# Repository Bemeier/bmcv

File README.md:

# BMCV

Eight scene-crossfaded LFOs in 16HP, with a PLL that locks them to an incoming
clock. This repository is the firmware, and three other things that run the
*same* firmware: a headless simulator, a browser frontend, and a VCV Rack
module.

**[bemeier.github.io/bmcv](https://bemeier.github.io/bmcv/)** is that frontend,
built and deployed from `main`. It runs the module with no install, shows a
physical one over USB if you have the hardware, and carries the
[manual](https://bemeier.github.io/bmcv/manual/), a
[firmware updater](https://bemeier.github.io/bmcv/update/) and a
[diagnostics page](https://bemeier.github.io/bmcv/diagnostics/).

How to *play* the module is the manual's job, not this file's. What follows is
how the project is put together.

## One core, four hosts

Everything that behaves like a BMCV runs `Core/Src/Lib` unmodified - the same
`engine_tick`, the same UX layer, the same LED renderer. Nothing below
reimplements any of it, and none of them may: a host supplies time, input and
somewhere to put the output, and that is the whole contract.

| | what it is | lives in |
|---|---|---|
| **Firmware** | The module. STM32G474, one `bmcv_main()` off a 250µs tick. | `Core/Src/` |
| **Simulator** | The same core behind a flat C API, plus a scripting CLI for golden-file runs. | `sim/` |
| **Web frontend** | That API compiled to wasm, with an SVG panel and scopes over it. | `web/` |
| **VCV Rack** | A Rack module wrapping the same core. | `vcv/` |

The consequence worth knowing: the browser page is not a *model* of the module,
it is the module's own code with a different set of peripherals bolted on. That
is what lets the same page decode a real module's memory - see
[docs/live-module.md](docs/live-module.md) - with no parser and no second copy
of any unit conversion.

[docs/architecture.md](docs/architecture.md) is the long version.

## Repository layout

    Core/Src/Lib/     the core: engine, UX layer, LED renderer. No hardware.
    Core/Src/         the firmware's own half: ADCs, DAC, FRAM, USB, main loop.
    USB_Device/       the USB stack's app layer - descriptors, WebUSB, DFU entry.
    Middlewares/      ST's USB device library, with the MIDI class extended.

    sim/              the flat C API, its runtime shims and the scripting CLI.
    web/              the browser frontend: simulator, manual, updater, diagnostics.
    vcv/              the VCV Rack plugin.

    tests/            host-compiled tests over Core/Src/Lib and the USB descriptors.
    tools/            code generators - the panel spec, the layout asserts.
    panel/            the generated panel spec, shared by every host.
    pcb/              the KiCad project; production/ holds its fab outputs.
    docs/             architecture, the PLL, the wavetable, the live link, setup.

`Core/Src/Lib` never includes a HAL header. That is what makes the same files
compile for ARM, for the host tests, for wasm and for Rack - and it holds
because three of those four toolchains have no STM32 headers at all.

## Hardware

BMCV is a real Eurorack module - a Macro CV Controller inspired by the
[Emblematic Systems Catalyst](http://www.emblematic-systems.net/). The PCB is
made with [KiCad 8.0](https://www.kicad.org/); the project lives in
[`pcb/`](pcb/) and its fabrication outputs (BOM, gerbers, pick-and-place) in
[`production/`](production/).

![Render][render]

Eight output jacks and four input jacks, eight endless encoders that are also
buttons, nine control buttons, seven scene buttons, a crossfader, and 21
WS2812s. One USB-C port, which is a MIDI port and a vendor interface at once -
[docs/midi.md](docs/midi.md), [docs/live-module.md](docs/live-module.md).

The panel geometry is not typed in anywhere. `tools/gen_panel_spec.py` reads the
KiCad placement data and the firmware's own index tables and writes `panel/`,
which every host then draws from - so the picture on the web page cannot drift
from the board.

## The concepts the design turns on

Three, and most of the codebase follows from them.

**A channel is an oscillator locked to a ratio, not a rate.** Frequencies are
divisions of the incoming beat, so a patch stays in phase with everything around
it. That is why there is a PLL rather than a tempo readout, and why
`clock_sync.c` is the most carefully tested file here -
[docs/pll.md](docs/pll.md).

**A scene is every parameter of every channel at once, and the crossfader blends
two of them.** Forty-eight values move on one fader. That is why parameters live
in a scene-indexed array rather than on the channel, and why `EngineConfig` is
the thing that gets saved, copied and cleared.

**The whole module is one struct.** `BmcvInstance` holds the config, the signal
path, the interaction state and the input layer; the firmware keeps exactly one.
Nothing that matters lives in a file-static. That is what lets a host run
several, a test build one per case, and a debug probe or a USB link ship the
entire module to a browser as bytes.

## LED language

The colours are not decoration. One fact per LED, and the same colour for the
same idea on every page - the point being that the panel teaches itself, so the
manual never has to explain a colour.

- **Ctrl-page settings clamp, they do not wrap.** Each is a short list of
  unrelated states with its default at index 0, so spinning an encoder fully
  left resets it and you can do that without looking. Rolling off one end into
  the other would be the largest change on the page.
- **Setting states** are the base layer. Index 0 of every setting - disabled,
  default, neutral - is **purple**; **cyan** is continuous / level-following or
  multiplicative, **green** additive or half-way, **yellow** triggered / clocked
  / stepped, **red** reset. Destructive is **pink**, and belongs to clearing
  alone. See `HUE_STATE_*` in `color_presets.h`. The output clamp is the one
  place brightness also carries meaning, because it is two facts on one LED.
- **White is assignment, and nothing else uses it.** A short white flash every
  1.6s over an element's own colour means "you can pick this". Once something is
  held, the places it can go are steady white with a short dropout, the held
  source is steady saturated purple, and everything else goes **dark** - if it
  cannot be pressed it does not light.
- **Output level** only appears when no shift mode is active. In a shift mode
  the encoder ring shows that mode's setting, or nothing if it has none.
- **FRQ is a ratio, not a level**, so its ring codes three facts on three axes
  rather than drawing a bar. **Hue** is the kind of division: **green** straight
  (halves, quarters, octaves), **yellow** triplet, **orange** quintuplet -
  octaves are free, so 1/8 and 16 are the same green and 1/3, 3/2 and 24 are the
  same yellow. **Saturation** is how far off the grid the value sits, so a fine
  adjust washes the colour out to a pastel and a snapped ratio is pure.
  **Brightness** pulses shallowly at the channel's own output rate, which is
  what says fast from slow; anything too fast for the panel to resolve shimmers
  together at one rate instead of aliasing into a slow phantom pulse.
- **Confirmations** are a brief flash on top: purple wrote, pink cleared, cyan
  loaded. Purple is the selection colour, so a copy landing somewhere flashes
  the colour the source was held in. Red is errors only.
- **A held press dips out once as it crosses each of its thresholds** - off,
  then back on - which says "that registered" rather than pulsing away as if
  something were still in progress. At the first stage it comes back exactly as
  the page had it; where holding longer does something wider - clearing every
  scene rather than this one - it comes back brighter, in the same colour.
  Nothing commits until the release.

## Building

Prerequisites, what each fetch recipe actually gets and why, and
troubleshooting: [docs/setup.md](docs/setup.md). On a fresh checkout, the one
thing to run first is `just arm-sdk`.

    just arm-sdk          # fetch the ARM toolchain + STM32Cube HAL, once
    just build            # ARM firmware        just flash / just flash-usb
    just check            # everything host-side: format, tests, flows, wasm, web
    just check-all        # the above plus the firmware and Rack plugin builds
    just test-san         # the same tests under ASan/UBSan
    just fmt              # clang-format the hand-written C (fmt-check to verify)
    just web              # the browser frontend, at http://localhost:8000
    just docs-page        # the same pages with no wasm build, for the updater
    just vcv-install      # build the Rack plugin into ~/.local/share/Rack2
    just vcv-dist win-x64 # a distributable .vcvplugin for any platform

    # Rack running on Windows while you build in WSL. Needs the cross-compiler
    # once: sudo apt install gcc-mingw-w64-x86-64 g++-mingw-w64-x86-64
    just vcv-win-install  # cross-build plugin.dll into %LOCALAPPDATA%\Rack2

    just panel            # regenerate the panel spec from the hardware repo
    just layout-check     # regenerate the struct layout asserts from the ELF
    just docs-shots       # regenerate the screenshots in this file
    just dfu-check        # check the DfuSe client against a fake device

`just fmt` is pinned to clang-format 18, which is what CI installs; the recipe
refuses any other major, because the output moves between them.

Anything machine-specific - where your Rack SDK lives, which browser to drive -
goes in `local.just`, which is not checked in. `CMakeLists.txt` has the same
arrangement with `local.cmake`.

CI runs `just check`, the sanitizer pass and an ARM build on every push - one
job per target, in [`.github/workflows/ci.yml`](.github/workflows/ci.yml). The
firmware size is printed into the job summary rather than gated.

A push to `main` that clears every job bumps `VERSION` and `CHANGELOG.md` from
the commits since the last tag and cuts a GitHub Release - see
[Versioning](#versioning). The same push deploys `web/` to GitHub Pages.

## Flashing

Three routes, and they want different files.

**Over the programming header, from a build.** `just flash` sends
`build/BMCVFirmware.elf` over an ST-Link; `just flash-rel` does the same with
the release build. It needs the module out of the rack with a ribbon on its
debug header, and it is the only route that can also halt the core - so it is
what `just where` and any breakpoint work sit on.

**Over USB-C, from a build.** `just flash-usb` sends `build/BMCVFirmware.bin`
through the STM32's ROM DFU bootloader, with no probe and **the module still in
the rack**. That is the development loop when nothing needs stepping through:
the WebUSB link and the diagnostics page still work, so printf-level debugging
survives; halting does not. The module has to be put into update mode first -
hold **CPY** while it powers up, or press the update-mode button on the updater
page - and the recipe says which, then waits for the bootloader to appear. See
[docs/setup.md](docs/setup.md).

**Over USB-C, from the browser.**
[bemeier.github.io/bmcv/update](https://bemeier.github.io/bmcv/update/) flashes
a released version or a local `.bin`, with no build and no probe. `just
docs-page` serves the same page locally against your own build. That page
documents the rest - what to hold, what Windows needs once, what the panel does
- and this file does not repeat it.

It has to be the `.bin` there. The `.elf` beside it is what the ST-Link path
wants and is not a raw image: headers and symbols, so its first bytes are not
the vector table, and a debug build is four times the size of the flash. The
updater checks for this and refuses, naming the mistake, before erasing
anything.

Both files are on every [release](https://github.com/Bemeier/bmcv/releases). The
`.elf` is the same build with its symbols still attached, which is what a
debugger or a live variable viewer needs to attach to a module running that
release - a `.bin` carries no symbol table, so no tool can find a variable in
one. Take the `.elf` from the release the module is actually running, since
every address in it belongs to that build.

## Installing the Rack module without building it

Every [release](https://github.com/Bemeier/bmcv/releases) carries a
`BMCV-<version>-<platform>.vcvplugin` for `lin-x64`, `win-x64`, `mac-x64` and
`mac-arm64`. Drop the one for your platform into Rack's plugin folder and
restart Rack, which unpacks it on the way up. The folder ends in your
platform's name - since Rack 2.4 there is one per platform, and a plain
`plugins` directory is not read:

| | |
|---|---|
| Windows | `%LOCALAPPDATA%\Rack2\plugins-win-x64` |
| macOS (Apple silicon) | `~/Library/Application Support/Rack2/plugins-mac-arm64` |
| macOS (Intel) | `~/Library/Application Support/Rack2/plugins-mac-x64` |
| Linux | `~/.local/share/Rack2/plugins-lin-x64` |

It is not in the VCV Library, so nothing has signed it but this repository's
CI. On macOS that means Gatekeeper quarantines it on download and Rack then
refuses to load it - clear the flag on the file itself, before starting Rack:

    xattr -dr com.apple.quarantine ~/Library/Application\ Support/Rack2/plugins-mac-arm64/BMCV-*.vcvplugin

Windows may want a "more info" click past SmartScreen the first time.

## Versioning

Commit messages are [Conventional Commits](https://www.conventionalcommits.org)
- `feat: ...`, `fix: ...`, `feat!: ...` for a breaking change, and so on -
enforced on pull requests by the `commits` CI job. `VERSION` and
`CHANGELOG.md` are generated from them by [commitizen](https://commitizen-tools.github.io/commitizen/),
never edited by hand; `Core/Inc/Lib/version.h` is in turn generated from
`VERSION` at configure time, which is why it isn't checked in.

    just commit          interactive wizard for a correctly formatted message
    just bump-dry-run    preview the next version and changelog, unattended
    just bump            bump, commit and tag locally - or just push to main
                         and let the `release` CI job do it

Needs `pipx install commitizen` (or `pip install --user commitizen`) once.

The Rack plugin is the one thing that does not follow this version, because it
cannot: Rack refuses to load a plugin whose version does not begin with Rack's
own major, so driving `vcv/plugin.json` from `VERSION` would pin this project's
major to Rack's and cost the firmware its semver. It is fixed at `2.0.0` and
stays there - it means "for Rack 2", not "the second version of anything". The
firmware version travels on the released file's name instead,
`BMCV-v0.6.1-lin-x64.vcvplugin`, which is why the plugin shows as 2.0.0 in
Rack's browser however new the firmware inside it is.

## License

This work is licensed under a [Creative Commons Attribution-ShareAlike 4.0 International License][cc].

[![CC BY SA 4.0][shield]][cc]

[cc]: https://creativecommons.org/licenses/by-sa/4.0
[shield]: https://licensebuttons.net/l/by-sa/4.0/88x31.png
[render]: https://raw.githubusercontent.com/Bemeier/bmcv/refs/heads/main/pcb/render.png

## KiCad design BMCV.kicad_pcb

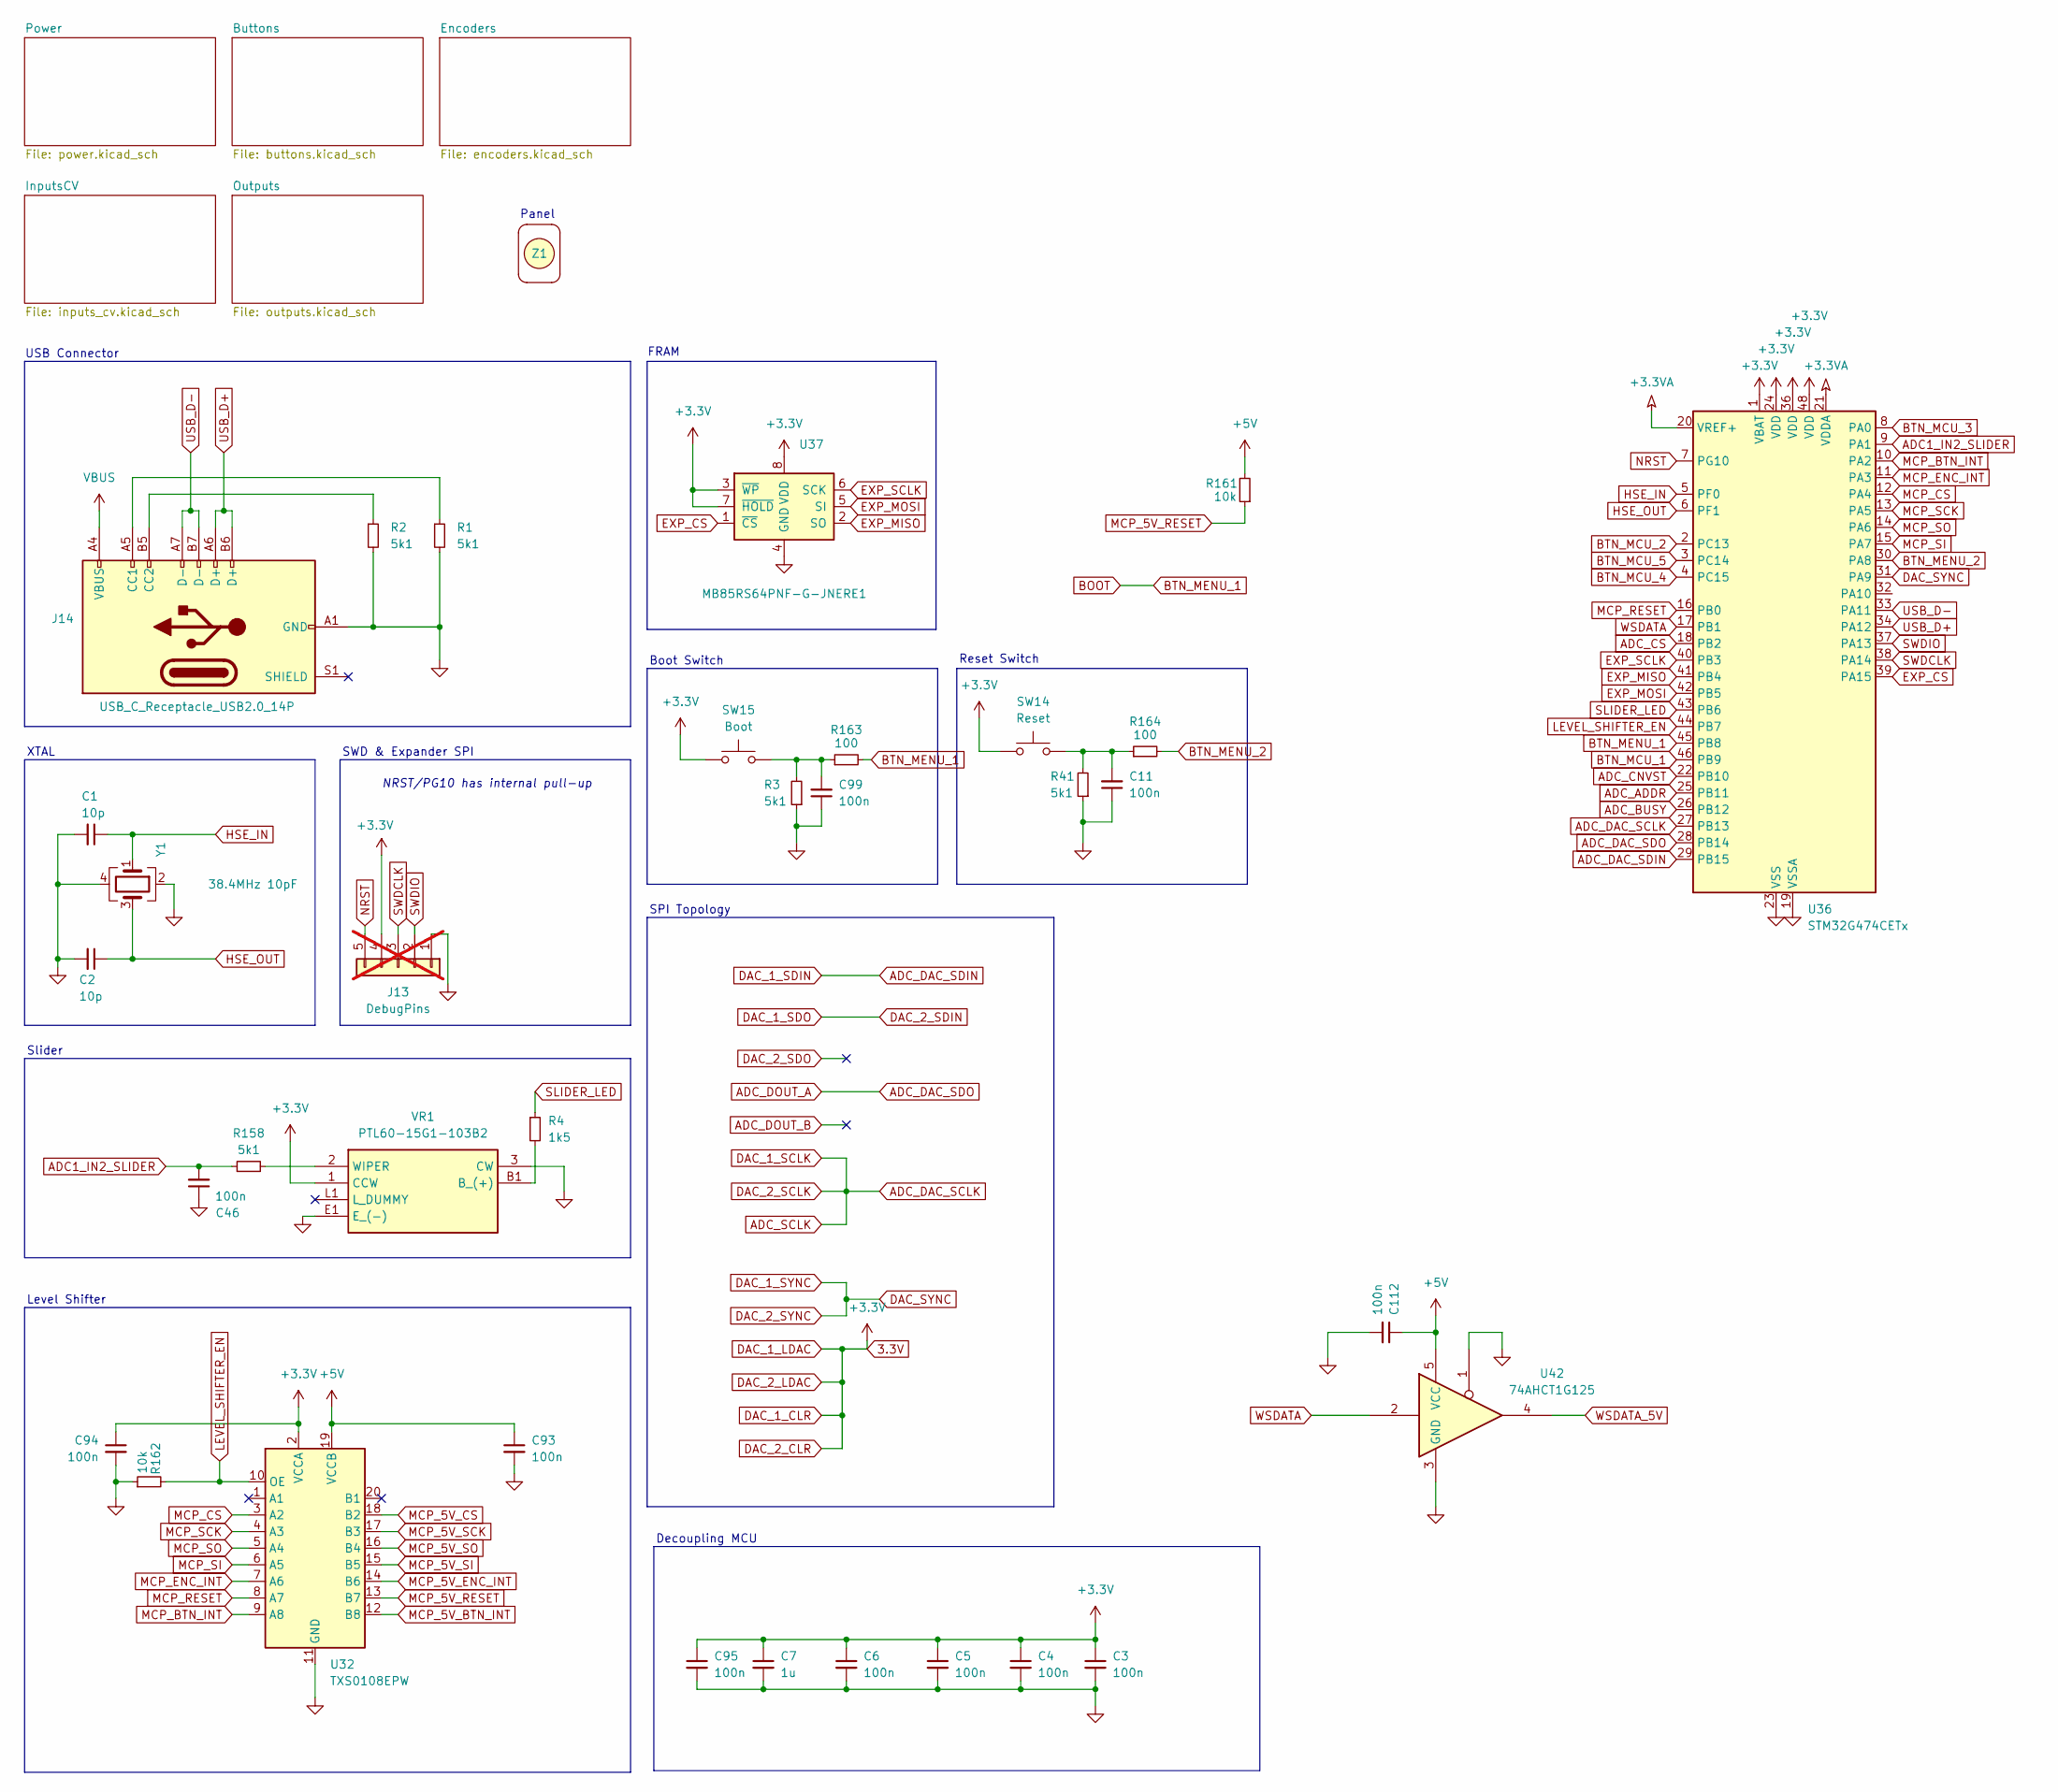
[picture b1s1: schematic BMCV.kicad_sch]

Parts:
C1, C2: 10p; C_0402_1005Metric; LCSC Part # C161520
C3, C4, C5, C6, C11, C46, C93, C94, C95, C99, C112: 100n; C_0402_1005Metric; LCSC Part # C307331
C7: 1u; C_0603_1608Metric; LCSC Part # C15849
J13: DebugPins; PinSocket_1x05_P2.54mm_Vertical; not fitted
J14: USB_C_Receptacle_USB2.0_14P; GT-USB-7035E; LCSC Part # C22384784
R1, R2, R3, R41, R158: 5k1; R_0402_1005Metric; LCSC Part # C25905
R4: 1k5; R_0603_1608Metric; LCSC Part # C22843
R161, R162: 10k; R_0402_1005Metric; LCSC Part # C25744
R163, R164: 100; R_0402_1005Metric; LCSC Part # C25076
SW14: Reset; TS-1095PS-AXXBX-C3DX; LCSC Part # C2834959
SW15: Boot; TS-1095PS-AXXBX-C3DX; LCSC Part # C2834959
U32: TXS0108EPW; TSSOP-20_4.4x6.5mm_P0.65mm; LCSC Part # C17206
U36: STM32G474CETx; LQFP-48_7x7mm_P0.5mm; LCSC Part # C730125
U37: MB85RS64PNF-G-JNERE1; SSOP-8_3.9x5.05mm_P1.27mm; LCSC Part # C8741
U42: 74AHCT1G125; SOT-353_SC-70-5
VR1: PTL60-15G1-103B2; PTL6015xxxxxxx; Mouser Part Number 652-PTL60-15G1-103B2
Y1: 38.4MHz 10pF; Crystal_SMD_2520-4Pin_2.5x2.0mm; LCSC Part # C3020671
Z1: BMCVPanel

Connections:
3.3V: C3.1, C4.1, C5.1, C6.1, C7.1, C94.1, C95.1, J13.4, SW14.1, SW15.1, U32.2 (VCCA), U36.1 (VBAT), U36.24 (VDD), U36.36 (VDD), U36.48 (VDD), U37.3 (~WP), U37.7 (~HOLD), U37.8 (VDD), VR1.1 (CCW); also elsewhere on the board
+3.3VA: U36.20 (VREF+), U36.21 (VDDA); also elsewhere on the board
+5V: C93.1, C112.1, R161.2, U32.19 (VCCB), U42.5 (VCC); also elsewhere on the board
ADC1_IN2_SLIDER: C46.2, R158.1, U36.9 (PA1)
ADC_ADDR: U36.25 (PB11); also elsewhere on the board
ADC_BUSY: U36.26 (PB12); also elsewhere on the board
ADC_CNVST: U36.22 (PB10); also elsewhere on the board
ADC_CS: U36.18 (PB2); also elsewhere on the board
ADC_DAC_SCLK: U36.27 (PB13); also elsewhere on the board
ADC_DAC_SDIN: U36.29 (PB15); also elsewhere on the board
ADC_DAC_SDO: U36.28 (PB14); also elsewhere on the board
BOOT: R163.2, U36.45 (PB8)
BTN_MCU_1: U36.46 (PB9); also elsewhere on the board
BTN_MCU_2: U36.2 (PC13); also elsewhere on the board
BTN_MCU_3: U36.8 (PA0); also elsewhere on the board
BTN_MCU_4: U36.4 (PC15); also elsewhere on the board
BTN_MCU_5: U36.3 (PC14); also elsewhere on the board
BTN_MENU_2: R164.2, U36.30 (PA8)
DAC_1_SYNC: U36.31 (PA9); also elsewhere on the board
EXP_CS: U36.39 (PA15), U37.1 (~CS)
EXP_MISO: U36.41 (PB4), U37.2 (SO)
EXP_MOSI: U36.42 (PB5), U37.5 (SI)
EXP_SCLK: U36.40 (PB3), U37.6 (SCK)
GND: C1.2, C2.2, C3.2, C4.2, C5.2, C6.2, C7.2, C11.1, C46.1, C93.2, C94.2, C95.2, C99.1, C112.2, J13.1, J14.A1 (GND), J14.A12 (GND), J14.B1 (GND), J14.B12 (GND), R1.2, R2.2, R3.1, R41.1, R162.1, U32.11 (GND), U36.19 (VSSA), U36.23 (VSS), U36.35 (VSS), U36.47 (VSS), U37.4 (GND), U42.1, U42.3 (GND), VR1.3 (CW), VR1.E1 (E_(-)), Y1.2, Y1.4; also elsewhere on the board
HSE_IN: C1.1, U36.5 (PF0), Y1.1
HSE_OUT: C2.1, U36.6 (PF1), Y1.3
LEVEL_SHIFTER_EN: R162.2, U32.10 (OE), U36.44 (PB7)
MCP_5V_BTN_INT: U32.12 (B8); also elsewhere on the board
MCP_5V_CS: U32.18 (B2); also elsewhere on the board
MCP_5V_ENC_INT: U32.14 (B6); also elsewhere on the board
MCP_5V_RESET: R161.1, U32.13 (B7); also elsewhere on the board
MCP_5V_SCK: U32.17 (B3); also elsewhere on the board
MCP_5V_SI: U32.15 (B5); also elsewhere on the board
MCP_5V_SO: U32.16 (B4); also elsewhere on the board
MCP_BTN_INT: U32.9 (A8), U36.10 (PA2)
MCP_CS: U32.3 (A2), U36.12 (PA4)
MCP_ENC_INT: U32.7 (A6), U36.11 (PA3)
MCP_RESET: U32.8 (A7), U36.16 (PB0)
MCP_SCK: U32.4 (A3), U36.13 (PA5)
MCP_SI: U32.6 (A5), U36.15 (PA7)
MCP_SO: U32.5 (A4), U36.14 (PA6)
NRST: J13.5, U36.7 (PG10)
unnamed: C11.2, R41.2, R164.1, SW14.2
unnamed: C99.2, R3.2, R163.1, SW15.2
unnamed: J14.A5 (CC1), R1.1
unnamed: J14.B5 (CC2), R2.1
unnamed: R4.2, VR1.B1 (B_(+))
unnamed: R158.2, VR1.2 (WIPER)
SLIDER_LED: R4.1, U36.43 (PB6)
SWDCLK: J13.3, U36.38 (PA14)
SWDIO: J13.2, U36.37 (PA13)
USB_D+: J14.A6 (D+), J14.B6 (D+), U36.34 (PA12)
USB_D-: J14.A7 (D-), J14.B7 (D-), U36.33 (PA11)
VBUS: J14.A4 (VBUS), J14.A9 (VBUS), J14.B4 (VBUS), J14.B9 (VBUS)
WSDATA: U36.17 (PB1), U42.2
WSDATA_5V: U42.4; also elsewhere on the board

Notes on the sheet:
SPI Topology
NRST/PG10 has internal pull-up
Boot Switch
Slider
Panel
Reset Switch
Level Shifter
Decoupling MCU
USB Connector
XTAL
SWD & Expander SPI
FRAM

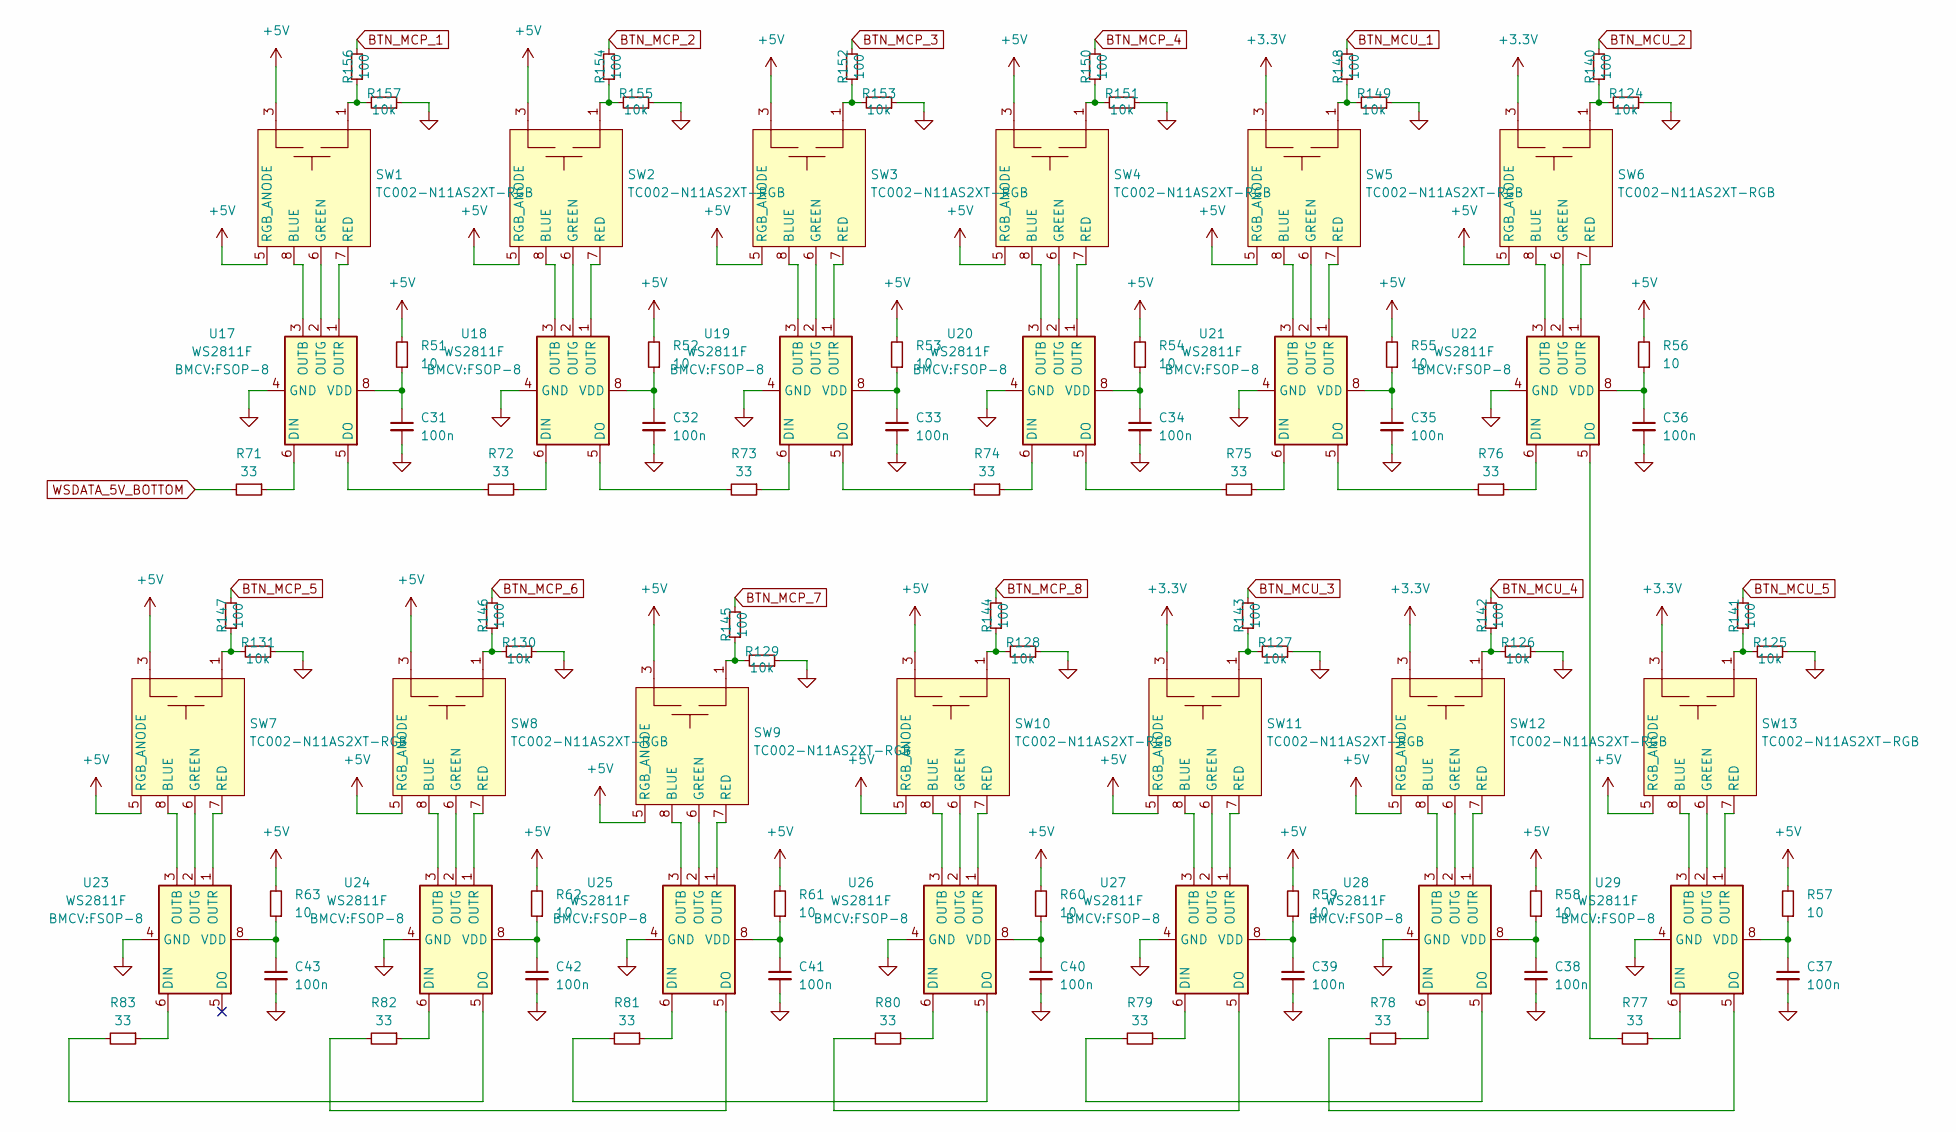
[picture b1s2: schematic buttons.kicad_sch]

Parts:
C31, C32, C33, C34, C35, C36, C37, C38, C39, C40, C41, C42, C43: 100n; C_0402_1005Metric; LCSC Part # C307331
R51, R52, R53, R54, R55, R56, R57, R58, R59, R60, R61, R62, R63: 10; R_0402_1005Metric; LCSC Part # C25077
R71, R72, R73, R74, R75, R76, R77, R78, R79, R80, R81, R82, R83: 33; R_0402_1005Metric; LCSC Part # C25105
R124, R125, R126, R127, R128, R129, R130, R131, R149, R151, R153, R155, R157: 10k; R_0402_1005Metric; LCSC Part # C25744
R140, R141, R142, R143, R144, R145, R146, R147, R148, R150, R152, R154, R156: 100; R_0402_1005Metric; LCSC Part # C25076
SW1, SW2, SW3, SW4, SW5, SW6, SW7, SW8, SW9, SW10, SW11, SW12, SW13: TC002-N11AS2XT-RGB; TC002-N11AXXX-RGB
U17, U18, U19, U20, U21, U22, U23, U24, U25, U26, U27, U28, U29: WS2811F; FSOP-8; LCSC Part # C5446692

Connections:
3.3V: SW5.3, SW5.4, SW6.3, SW6.4, SW11.3, SW11.4, SW12.3, SW12.4, SW13.3, SW13.4; also elsewhere on the board
+5V: R51.2, R52.2, R53.2, R54.2, R55.2, R56.2, R57.2, R58.2, R59.2, R60.2, R61.2, R62.2, R63.2, SW1.3, SW1.4, SW1.5 (RGB_ANODE), SW2.3, SW2.4, SW2.5 (RGB_ANODE), SW3.3, SW3.4, SW3.5 (RGB_ANODE), SW4.3, SW4.4, SW4.5 (RGB_ANODE), SW5.5 (RGB_ANODE), SW6.5 (RGB_ANODE), SW7.3, SW7.4, SW7.5 (RGB_ANODE), SW8.3, SW8.4, SW8.5 (RGB_ANODE), SW9.3, SW9.4, SW9.5 (RGB_ANODE), SW10.3, SW10.4, SW10.5 (RGB_ANODE), SW11.5 (RGB_ANODE), SW12.5 (RGB_ANODE), SW13.5 (RGB_ANODE); also elsewhere on the board
BTN_MCP_1: R156.2; also elsewhere on the board
BTN_MCP_2: R154.2; also elsewhere on the board
BTN_MCP_3: R152.2; also elsewhere on the board
BTN_MCP_4: R150.2; also elsewhere on the board
BTN_MCP_5: R147.2; also elsewhere on the board
BTN_MCP_6: R146.2; also elsewhere on the board
BTN_MCP_7: R145.2; also elsewhere on the board
BTN_MCP_8: R144.2; also elsewhere on the board
BTN_MCU_1: R148.2; also elsewhere on the board
BTN_MCU_2: R140.2; also elsewhere on the board
BTN_MCU_3: R143.2; also elsewhere on the board
BTN_MCU_4: R142.2; also elsewhere on the board
BTN_MCU_5: R141.2; also elsewhere on the board
GND: C31.2, C32.2, C33.2, C34.2, C35.2, C36.2, C37.2, C38.2, C39.2, C40.2, C41.2, C42.2, C43.2, R124.1, R125.1, R126.1, R127.1, R128.1, R129.1, R130.1, R131.1, R149.1, R151.1, R153.1, R155.1, R157.1, U17.4 (GND), U18.4 (GND), U19.4 (GND), U20.4 (GND), U21.4 (GND), U22.4 (GND), U23.4 (GND), U24.4 (GND), U25.4 (GND), U26.4 (GND), U27.4 (GND), U28.4 (GND), U29.4 (GND); also elsewhere on the board
unnamed: R124.2, R140.1, SW6.1, SW6.2
unnamed: R125.2, R141.1, SW13.1, SW13.2
unnamed: R126.2, R142.1, SW12.1, SW12.2
unnamed: R127.2, R143.1, SW11.1, SW11.2
unnamed: R128.2, R144.1, SW10.1, SW10.2
unnamed: R129.2, R145.1, SW9.1, SW9.2
unnamed: R130.2, R146.1, SW8.1, SW8.2
unnamed: R131.2, R147.1, SW7.1, SW7.2
unnamed: R148.1, R149.2, SW5.1, SW5.2
unnamed: R150.1, R151.2, SW4.1, SW4.2
unnamed: R152.1, R153.2, SW3.1, SW3.2
unnamed: R154.1, R155.2, SW2.1, SW2.2
unnamed: R156.1, R157.2, SW1.1, SW1.2
unnamed: SW1.8 (BLUE), U17.3 (OUTB)
unnamed: SW1.6 (GREEN), U17.2 (OUTG)
unnamed: SW1.7 (RED), U17.1 (OUTR)
unnamed: SW2.8 (BLUE), U18.3 (OUTB)
unnamed: SW2.6 (GREEN), U18.2 (OUTG)
unnamed: SW2.7 (RED), U18.1 (OUTR)
unnamed: SW3.8 (BLUE), U19.3 (OUTB)
unnamed: SW3.6 (GREEN), U19.2 (OUTG)
unnamed: SW3.7 (RED), U19.1 (OUTR)
unnamed: SW4.8 (BLUE), U20.3 (OUTB)
unnamed: SW4.6 (GREEN), U20.2 (OUTG)
unnamed: SW4.7 (RED), U20.1 (OUTR)
unnamed: SW5.8 (BLUE), U21.3 (OUTB)
unnamed: SW5.6 (GREEN), U21.2 (OUTG)
unnamed: SW5.7 (RED), U21.1 (OUTR)
unnamed: SW6.8 (BLUE), U22.3 (OUTB)
unnamed: SW6.6 (GREEN), U22.2 (OUTG)
unnamed: SW6.7 (RED), U22.1 (OUTR)
unnamed: SW7.8 (BLUE), U23.3 (OUTB)
unnamed: SW7.6 (GREEN), U23.2 (OUTG)
unnamed: SW7.7 (RED), U23.1 (OUTR)
unnamed: SW8.8 (BLUE), U24.3 (OUTB)
unnamed: SW8.6 (GREEN), U24.2 (OUTG)
unnamed: SW8.7 (RED), U24.1 (OUTR)
unnamed: SW9.8 (BLUE), U25.3 (OUTB)
unnamed: SW9.6 (GREEN), U25.2 (OUTG)
unnamed: SW9.7 (RED), U25.1 (OUTR)
unnamed: SW10.8 (BLUE), U26.3 (OUTB)
unnamed: SW10.6 (GREEN), U26.2 (OUTG)
unnamed: SW10.7 (RED), U26.1 (OUTR)
unnamed: SW11.8 (BLUE), U27.3 (OUTB)
unnamed: SW11.6 (GREEN), U27.2 (OUTG)
unnamed: SW11.7 (RED), U27.1 (OUTR)
unnamed: SW12.8 (BLUE), U28.3 (OUTB)
unnamed: SW12.6 (GREEN), U28.2 (OUTG)
unnamed: SW12.7 (RED), U28.1 (OUTR)
unnamed: SW13.8 (BLUE), U29.3 (OUTB)
unnamed: SW13.6 (GREEN), U29.2 (OUTG)
unnamed: SW13.7 (RED), U29.1 (OUTR)
unnamed: R71.1, U17.6 (DIN)
unnamed: R72.2, U17.5 (DO)
unnamed: C31.1, R51.1, U17.8 (VDD)
unnamed: R72.1, U18.6 (DIN)
unnamed: R73.2, U18.5 (DO)
unnamed: C32.1, R52.1, U18.8 (VDD)
unnamed: R73.1, U19.6 (DIN)
unnamed: R74.2, U19.5 (DO)
unnamed: C33.1, R53.1, U19.8 (VDD)
unnamed: R74.1, U20.6 (DIN)
unnamed: R75.2, U20.5 (DO)
unnamed: C34.1, R54.1, U20.8 (VDD)
unnamed: R75.1, U21.6 (DIN)
unnamed: R76.2, U21.5 (DO)
unnamed: C35.1, R55.1, U21.8 (VDD)
unnamed: R76.1, U22.6 (DIN)
unnamed: R77.2, U22.5 (DO)
unnamed: C36.1, R56.1, U22.8 (VDD)
unnamed: R83.1, U23.6 (DIN)
unnamed: C43.1, R63.1, U23.8 (VDD)
unnamed: R82.1, U24.6 (DIN)
unnamed: R83.2, U24.5 (DO)
unnamed: C42.1, R62.1, U24.8 (VDD)
unnamed: R81.1, U25.6 (DIN)
unnamed: R82.2, U25.5 (DO)
unnamed: C41.1, R61.1, U25.8 (VDD)
unnamed: R80.1, U26.6 (DIN)
unnamed: R81.2, U26.5 (DO)
unnamed: C40.1, R60.1, U26.8 (VDD)
unnamed: R79.1, U27.6 (DIN)
unnamed: R80.2, U27.5 (DO)
unnamed: C39.1, R59.1, U27.8 (VDD)
unnamed: R78.1, U28.6 (DIN)
unnamed: R79.2, U28.5 (DO)
unnamed: C38.1, R58.1, U28.8 (VDD)
unnamed: R77.1, U29.6 (DIN)
unnamed: R78.2, U29.5 (DO)
unnamed: C37.1, R57.1, U29.8 (VDD)
WSDATA_5V_BOTTOM: R71.2; also elsewhere on the board

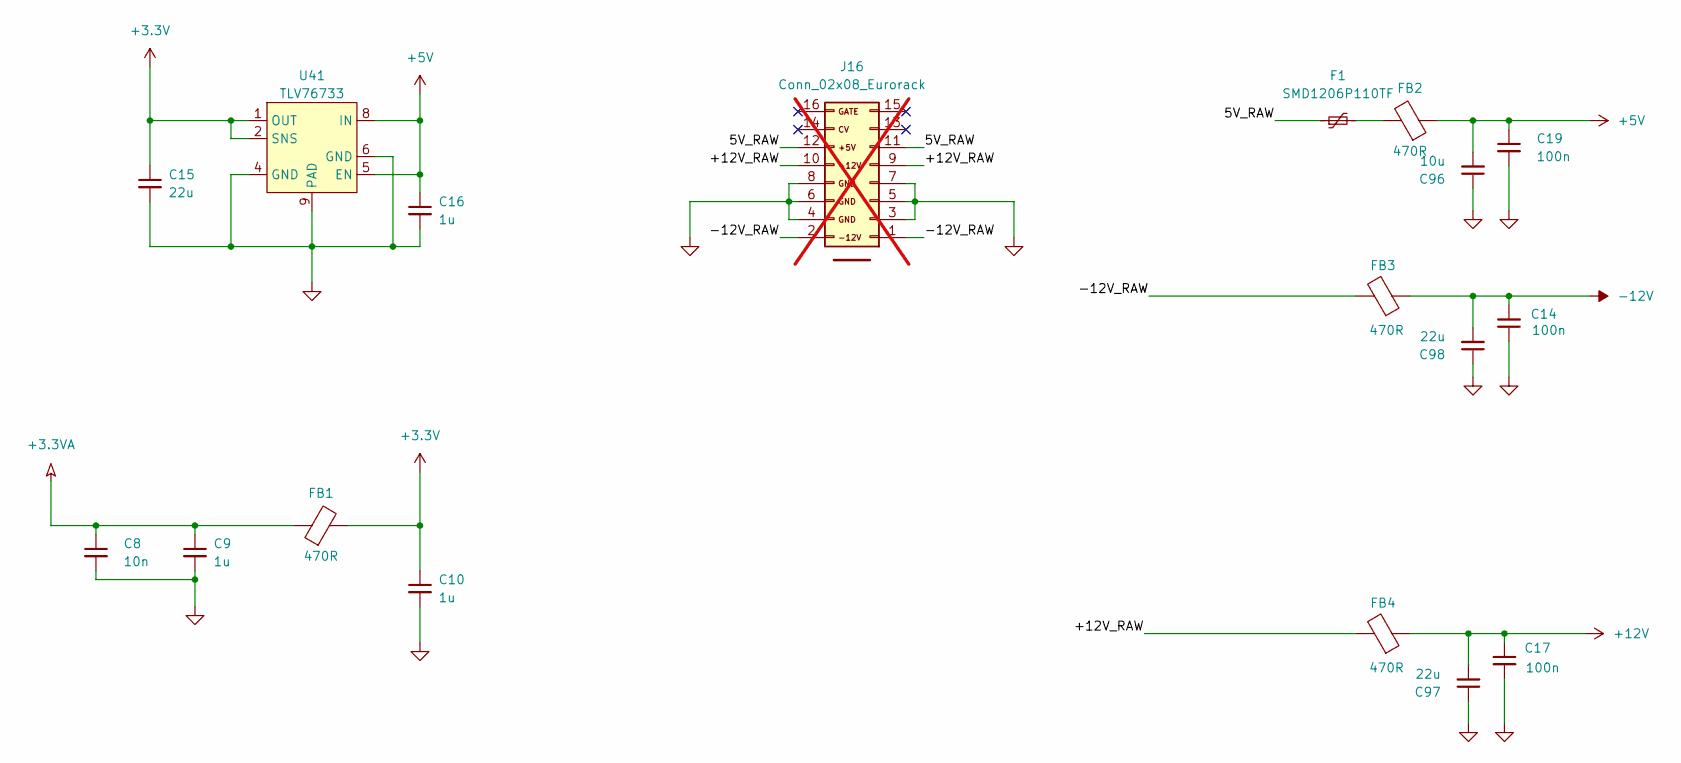
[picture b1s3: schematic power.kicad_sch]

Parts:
C8: 10n; C_0402_1005Metric; LCSC Part # C15195
C9, C10, C16: 1u; C_0603_1608Metric; LCSC Part # C15849
C14, C17, C19: 100n; C_0603_1608Metric; LCSC Part # C14663
C15, C97, C98: 22u; C_0805_2012Metric; LCSC Part # C45783
C96: 10u; C_0805_2012Metric; LCSC Part # C237493
F1: SMD1206P110TF; Fuse_1206_3216Metric; LCSC Part # C20801
FB1, FB2, FB3, FB4: 470R; L_0603_1608Metric; LCSC Part # C114780
J16: Conn_02x08_Eurorack; Eurorack_Full_IDC_Vertical; LCSC Part # C3406; not fitted
U41: TLV76733; HVSSOP-8-1EP_3x3mm_P0.65mm_EP1.57x1.89mm; LCSC Part # C2873382

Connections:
3.3V: C10.1, C15.1, FB1.2, U41.1 (OUT), U41.2 (SNS); also elsewhere on the board
+3.3VA: C8.1, C9.1, FB1.1; also elsewhere on the board
+5V: C16.1, C19.1, C96.2, FB2.1, U41.5 (EN), U41.8 (IN); also elsewhere on the board
+12V: C17.1, C97.2, FB4.1; also elsewhere on the board
-12V: C14.2, C98.2, FB3.1; also elsewhere on the board
/Power/5V_RAW: F1.1, J16.11, J16.12
/Power/+12V_RAW: FB4.2, J16.9, J16.10
/Power/-12V_RAW: FB3.2, J16.1, J16.2
GND: C8.2, C9.2, C10.2, C14.1, C15.2, C16.2, C17.2, C19.2, C96.1, C97.1, C98.1, J16.3, J16.4, J16.5, J16.6, J16.7, J16.8, U41.4 (GND), U41.6 (GND), U41.9 (PAD); also elsewhere on the board
unnamed: F1.2, FB2.2
